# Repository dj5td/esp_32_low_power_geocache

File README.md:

# ESP 32 low power geocache

## Idea and Goals

### Idea

### Goals

## Schematic

## Parts
You can find a bill of materials (BOM) file for LCSC in the repository. Not included are pinheaders, solar panel and the lithium-ion battery.
## Software
Software will be developed once I received and built the first prototype. Hang in there.
## License

This project is licensed under the Creative Commons Attribution-NonCommercial-ShareAlike 4.0 International licence. See the [LICENSE.md](LICENSE.md) file for details.
## Acknowledgments
Special thanks go out to my amateur radio friends who helped me a lot during design of the schematic and PCB:
* Mathias Weyland
* Oliver
* Rune Broberg

You guys show us that amateur radio still is about experimenting with hardware and software, and that it is even more amazing to do so nowadays than ever before. This international community is amazing and I encourage everyone interested in tinkering, creating and engineering to join us.

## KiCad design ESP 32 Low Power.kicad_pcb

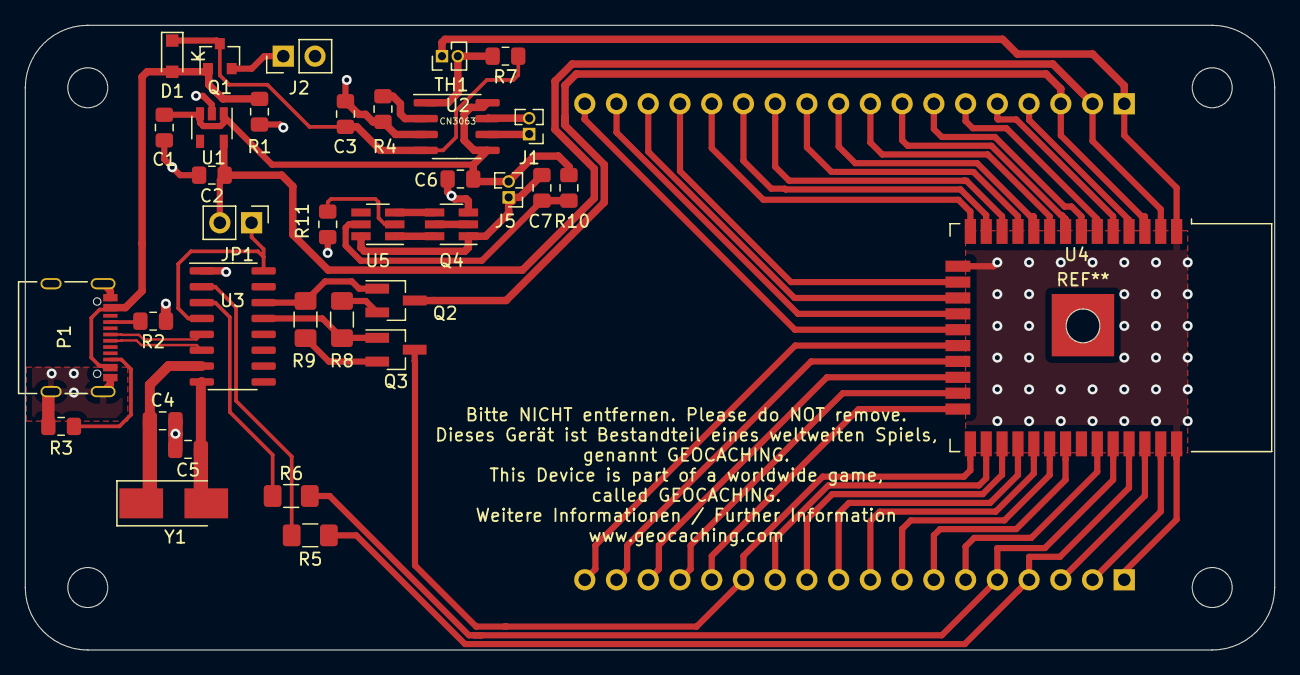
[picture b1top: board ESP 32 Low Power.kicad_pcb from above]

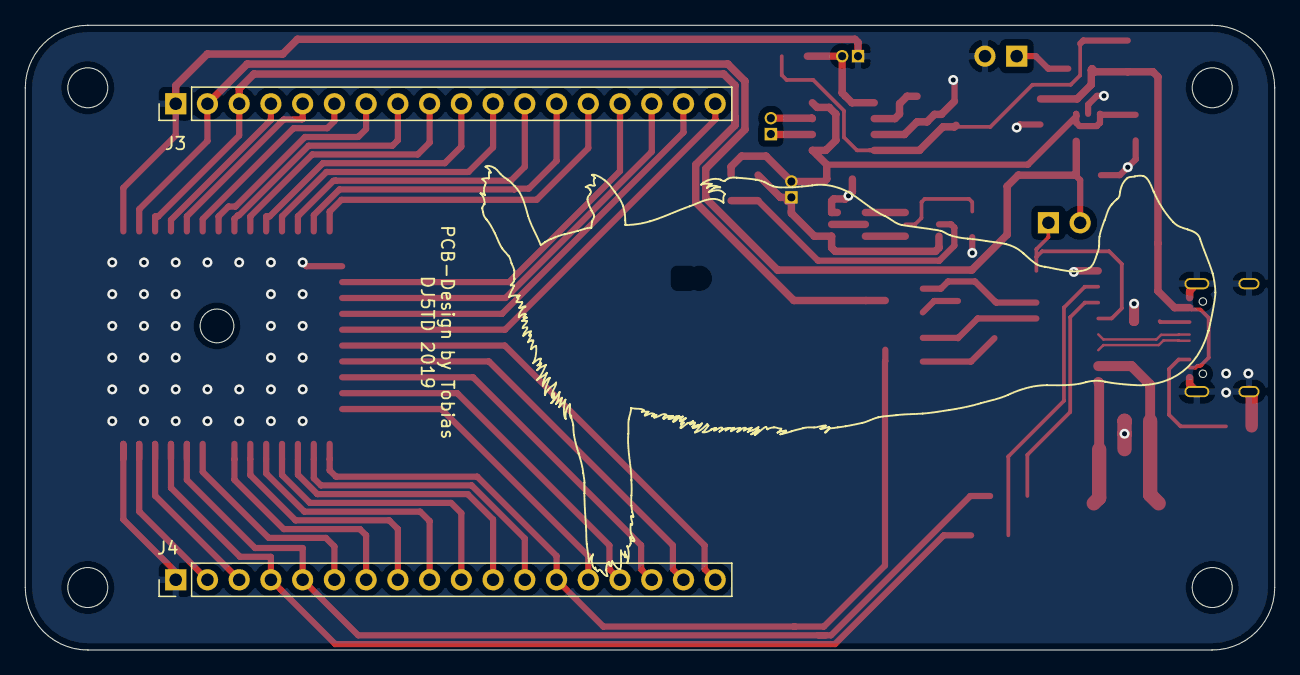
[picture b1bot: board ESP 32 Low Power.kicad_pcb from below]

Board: 2 copper layers, 100.0 x 50.0 mm, 37 parts (2 on the bottom side), 62 nets.

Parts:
C1, C2: 10uF; C_0805_2012Metric_Pad1.15x1.40mm_HandSolder
C3, C6: 4.7uF; C_0805_2012Metric_Pad1.15x1.40mm_HandSolder
C4, C5: 22pF; C_0805_2012Metric_Pad1.15x1.40mm_HandSolder
C7: 0.1uF; C_0805_2012Metric_Pad1.15x1.40mm_HandSolder
D1: 1N5817; D_SOD-323_HandSoldering
J1: Conn_01x02; PinHeader_1x02_P1.27mm_Vertical
J2: Conn_01x02; PinHeader_1x02_P2.54mm_Vertical
J3, J4: Conn_01x18; PinHeader_1x18_P2.54mm_Vertical
J5: Battery; PinHeader_1x02_P1.27mm_Vertical
JP1: Jumper_2_Open; PinHeader_1x02_P2.54mm_Vertical
P1: USB_C; USB_C_Receptacle_Palconn_UTC16-G
Q1: DMG2301L; SOT-23
Q2, Q3: S8050; SOT-23_Handsoldering
Q4: SE8810A; SOT-23-6_Handsoldering
R1, R11: 1K; R_0805_2012Metric_Pad1.15x1.40mm_HandSolder
R2, R3: 5.1K; R_0805_2012Metric_Pad1.15x1.40mm_HandSolder
R4: 3.6K; R_0805_2012Metric_Pad1.15x1.40mm_HandSolder
R5, R6: 470; R_1206_3216Metric_Pad1.42x1.75mm_HandSolder
R7: 4.7K; R_0805_2012Metric_Pad1.15x1.40mm_HandSolder
R8, R9: 12K; R_1206_3216Metric_Pad1.42x1.75mm_HandSolder
R10: 100R; R_0805_2012Metric_Pad1.15x1.40mm_HandSolder
TH1: Thermistor_NTC; PinHeader_1x02_P1.27mm_Vertical
U1: XC6220B331MR; SOT-23-5
U2: CN3063; SOIC-8_3.9x4.9mm_P1.27mm
U3: CH340G; SOIC-16_3.9x9.9mm_P1.27mm
U4: ESP32-WROOM-32
U5: DW01B; SOT-23-6_Handsoldering
Y1: 12 MHz; Crystal_SMD_5032-2Pin_5.0x3.2mm_HandSoldering

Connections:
+3V3: C2.1, J3.2, JP1.2, U1.5, U4.2
+5V: D1.2, P1.A4, P1.A9, P1.B4, P1.B9, Q1.1, R1.1
+BATT: C1.1, C6.1, J5.2, R10.2, U1.1, U1.3, U2.5, U2.8
/4: J3.4, U4.4
/5: J3.5, U4.5
/6: J3.6, U4.6
/7: J3.7, U4.7
/8: J3.8, U4.8
/9: J3.9, U4.9
/10: J3.10, U4.10
/11: J3.11, U4.11
/12: J3.12, U4.12
/13: J3.13, U4.13
/14: J3.14, U4.14
/16: J3.15, U4.16
/17: J3.16, U4.17
/18: J3.17, U4.18
/19: J3.18, U4.19
/20: J4.18, U4.20
/21: J4.17, U4.21
/22: J4.16, U4.22
/23: J4.15, U4.23
/24: J4.14, U4.24
/26: J4.12, U4.26
/27: J4.11, U4.27
/28: J4.10, U4.28
/29: J4.9, U4.29
/30: J4.8, U4.30
/31: J4.7, U4.31
/33: J4.6, U4.33
/36: J4.3, U4.36
/37: J4.2, U4.37
/CHIP_PU: J3.3, Q2.3, U4.3
/D+: P1.A6, U3.5
/D-: P1.A7, U3.6
/IO0: J4.13, Q3.3, U4.25
/RXD0: J4.5, R6.1, U4.34
/SOLAR_IN: J2.1, Q1.2
/TXD0: J4.4, R5.1, U4.35
GND: C1.2, C2.2, C3.2, C4.2, C5.2, C6.2, J2.2, J3.1, J4.1, P1.A1, P1.A12, P1.B1, P1.B12, P1.S1, Q4.3, R1.2, R2.1, R3.1, R4.2, R11.2, TH1.1, U1.2, U2.3, U3.1, U4.1, U4.15, U4.38
unnamed: C3.1, D1.1, Q1.3, R7.1, U2.4
unnamed: C4.1, U3.7, Y1.1
unnamed: C5.1, U3.8, Y1.2
unnamed: C7.1, R10.1, U5.5
unnamed: C7.2, J5.1, Q4.1, U5.6
unnamed: J1.1, U2.6
unnamed: J1.2, U2.7
unnamed: JP1.1, U3.4, U3.16
unnamed: P1.A5, R2.2
unnamed: P1.B5, R3.2
unnamed: Q2.1, R9.2, U3.14
unnamed: Q2.2, R8.1
unnamed: Q3.1, R8.2, U3.13
unnamed: Q3.2, R9.1
unnamed: Q4.2, Q4.5
unnamed: Q4.4, U5.3
unnamed: Q4.6, U5.1
unnamed: R4.1, U2.2
unnamed: R5.2, U3.2
unnamed: R6.2, U3.3
unnamed: R7.2, TH1.2, U2.1
unnamed: R11.1, U5.2

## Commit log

2019-08-24 First commit.
2019-08-26 Added battery low voltage protection
2019-08-26 Some better placement
2019-08-26 Add picture
